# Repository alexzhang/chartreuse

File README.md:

# chartreuse
Project Chartreuse: A touchscreen conbadge powered by Liiiinux!

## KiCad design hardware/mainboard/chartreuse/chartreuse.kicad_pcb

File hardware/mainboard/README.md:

# mainboard
The mainboard of the badge integrates:
- lithium-ion battery charge controller
- TTL LCD display driver
- sound card, amplifier, and speaker
- buttons, charging port, and indicator LEDs

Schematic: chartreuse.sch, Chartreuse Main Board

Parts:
C401, C402: 10uF; CP_Elec_4x5.8
FB1: BLM18RK601SN1D; R_0603
J1: USB_B_Micro; USB_Micro-B_Molex_47346-0001
J2: USB_B_Micro; Conn-5
J3: LiPo; JST_PH_S2B-PH-SM4-TB_02x2.00mm_Angled
J4: USB_A
U3: LM1117-3.3; SOT-223-3_TabPin2

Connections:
+3V3: C402.1, U3.2 (VO); also elsewhere on the board
+5V: C401.1, J2.1, J4.1, U3.3 (VI); also elsewhere on the board
/Power Supply/VCHARGE: J1.1; also elsewhere on the board
/Power Supply/VLIPO: J3.1; also elsewhere on the board
/USB Hub/USB_DOWN2_DN: J4.2; also elsewhere on the board
/USB Hub/USB_DOWN2_DP: J4.3; also elsewhere on the board
/USB Hub/USB_UP_DN: J2.2; also elsewhere on the board
/USB Hub/USB_UP_DP: J2.3; also elsewhere on the board
unnamed: FB1.1, J1.6

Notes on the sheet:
Charger Input
Raspberry Pi
Female USB-A Flash Drive

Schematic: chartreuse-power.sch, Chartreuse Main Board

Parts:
C101: 10uF; CP_Elec_4x5.8
C102: 10uF; C_0805
C103: 0.1uF; C_0402
C104: 2.2uF; C_0805
C105: 100uF; CP_Elec_5x5.8
D101: ORANGE; D_0805
D102: GREEN; D_0805
D103: RED; D_0805
L1: 6.8uH; L_Taiyo-Yuden_NR-40xx_HandSoldering
Q1: MMUN2133LT1G; SOT-23
R101: 270K; R_0402
R102, R104: 100K; R_0402
R103, R111, R112, R113: 1K; R_0402
R105: 15K; R_0402
R106, R109: 1.87M; R_0402
R107: 340K; R_0402
R108, R110: 200K; R_0402
SW1: SW_SPDT; SW_CuK_OS102011MA1QN1_SPDT_Angled
U1: MCP73871; QFN-20-1EP_4x4mm_Pitch0.5mm
U2: TPS61090; QFN-16-1EP_4x4mm_Pitch0.65mm

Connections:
+5V: C104.1, C105.1, R109.1, U2.1, U2.15, U2.16; also elsewhere on the board
/Power Supply/LOW_BATT: Q1.1, U2.12
/Power Supply/PWR_EN: R108.2, SW1.2, U2.11
/Power Supply/VBAT: C102.1, C103.1, L1.1, Q1.2, R106.1, R108.1, U1.1, U1.20, U2.8
/Power Supply/VCHARGE: D101.2, D102.2, R101.1, U1.3, U1.4, U1.9, U1.17, U1.18, U1.19; also elsewhere on the board
/Power Supply/VLIPO: C101.1, U1.14, U1.15, U1.16; also elsewhere on the board
unnamed: D101.1, R112.1
unnamed: D102.1, R113.1
unnamed: D103.2, R111.2
unnamed: L1.2, U2.3, U2.4
unnamed: Q1.3, R111.1
unnamed: R101.2, R102.1, U1.2
unnamed: R103.1, U1.13
unnamed: R104.1, U1.12
unnamed: R105.1, U1.5
unnamed: R106.2, R107.1, U2.9
unnamed: R109.2, R110.1, U2.14
unnamed: R112.2, U1.8
unnamed: R113.2, U1.7

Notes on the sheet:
Ceramic
Ceramic or Tantalum
On/Off Switch

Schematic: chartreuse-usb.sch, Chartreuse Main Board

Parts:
C201, C202, C203: 0.1uF; C_0402
C204: 10uF; C_0805
C205: 1uF; C_0402
C206, C207: 6pF; C_0402
FB2: BLM18RK601SN1D; R_0603
R201, R202, R203, R204: 56K; R_0402
U8: USB2422; QFN-24-1EP_4x4mm_Pitch0.5mm
Y1: 24M; Crystal_SMD_0603-4pin_6.0x3.5mm

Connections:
+3V3: FB2.2; also elsewhere on the board
/Display Controller/TOUCH_DN: U8.2; also elsewhere on the board
/Display Controller/TOUCH_DP: U8.3; also elsewhere on the board
/USB Hub/USB_DOWN2_DN: U8.4; also elsewhere on the board
/USB Hub/USB_DOWN2_DP: U8.5; also elsewhere on the board
/USB Hub/USB_UP_DN: U8.19; also elsewhere on the board
/USB Hub/USB_UP_DP: U8.20; also elsewhere on the board
unnamed: C201.1, C202.1, C203.1, C204.1, FB2.1, R201.1, U8.1, U8.9, U8.15, U8.16, U8.18
unnamed: C205.1, U8.10
unnamed: C206.1, U8.21, Y1.1
unnamed: C207.1, U8.22, Y1.3
unnamed: R201.2, U8.17
unnamed: R202.1, U8.13
unnamed: R203.1, U8.14
unnamed: R204.1, U8.24

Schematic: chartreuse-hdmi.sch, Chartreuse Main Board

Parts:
C301, C302, C303, C304, C326, C327, C328: 10uF; C_0805
C305, C306, C307, C308, C309, C310, C311, C312, C313, C314, C315, C316, C317, C322, C323, C331, C332: 0.1uF; C_0402
C318, C319, C320, C321: 103; C_0402
C324, C325: 12pF; C_0402
C329, C330: 1uF; C_0805
D301: RED; D_0805
D302: BLUE; D_0805
D303: MBR0540; D_SOD-123
D304: MM3Z24VT1G; D_SOD-323
D305: 1N4148; D_SOD-323
FB3, FB4, FB5, FB6, FB7, FB8, FB9: BLM18RK601SN1D; R_0603
FB10, FB11, FB12, FB13: Ferrite_Bead_Small; R_0603
J5: FFC-20; Conn-20
J6: FFC-40; HE10-40D
L2: BRL3225T150K; R_1210
Q2: BSS138; SOT-23
R301, R302, R303, R305, R307: 10K; R_0402
R304, R306: 1K; R_0402
R308: 3; R_0402
R309, R310: 12; R_0402
U4: TFP401A; TQFP-100-1EP_14x14mm_Pitch0.5mm
U5: 24LC02BT-OT; TSOT-23-5
U6: FAN5333; SOT-23-5
U7: AR1100-ISS; SOIC-20W_7.5x12.8mm_Pitch1.27mm
Y2: 12M; Resonator_SMD_muRata_CDSCB-2pin_4.5x2.0mm

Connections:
+3V3: C327.1, D302.2, FB3.2, FB4.2, FB5.2, FB6.2, FB7.1, J6.4; also elsewhere on the board
+5V: C326.1, C328.1, L2.1, R307.1, U6.5; also elsewhere on the board
/Display Controller/24V: C329.1, C330.1, D303.1, D304.1, J6.2
/Display Controller/ACTIVE: D305.1, J6.31, U4.8 (SCDT)
/Display Controller/AGND: C318.2, C319.2, C320.2, C321.2, C322.2, C323.2, C324.2, C325.2, FB8.1, FB9.1, R306.1, U7.6, U7.8, U7.9, U7.13, U7.20
/Display Controller/DISPEN: J6.34, U4.46 (DE)
/Display Controller/HDMI_5V: C332.1, J5.18, J5.19, J5.20, R301.1, R302.2, R303.2, U5.4
/Display Controller/HDMI_DDC_CLK: J5.15, R303.1, U5.1
/Display Controller/HDMI_DDC_DTA: J5.16, R302.1, U5.3
/Display Controller/HDMI_HOTPLUG: J5.17, R301.2
/Display Controller/HDMI_TMDS0_N: J5.8, U4.91 (RX0-)
/Display Controller/HDMI_TMDS0_P: J5.7, U4.90 (RX0+)
/Display Controller/HDMI_TMDS1_N: J5.5, U4.86 (RX1-)
/Display Controller/HDMI_TMDS1_P: J5.4, U4.85 (RX1+)
/Display Controller/HDMI_TMDS2_N: J5.2, U4.81 (RX2-)
/Display Controller/HDMI_TMDS2_P: J5.1, U4.80 (RX2+)
/Display Controller/HDMI_TMDSC_N: J5.11, U4.94 (RXC-)
/Display Controller/HDMI_TMDSC_P: J5.10, U4.93 (RXC+)
/Display Controller/HSYNC: J6.32, U4.48 (HSYNC)
/Display Controller/LEDK: C331.1, D304.2, J6.1, R308.1, R309.1, R310.1, U6.3
/Display Controller/OUT_B0: J6.21, U4.10 (QE0)
/Display Controller/OUT_B1: J6.22, U4.11 (QE1)
/Display Controller/OUT_B2: J6.23, U4.12 (QE2)
/Display Controller/OUT_B3: J6.24, U4.13 (QE3)
/Display Controller/OUT_B4: J6.25, U4.14 (QE4)
/Display Controller/OUT_B5: J6.26, U4.15 (QE5)
/Display Controller/OUT_B6: J6.27, U4.16 (QE6)
/Display Controller/OUT_B7: J6.28, U4.17 (QE7)
/Display Controller/OUT_G0: J6.13, U4.20 (QE8)
/Display Controller/OUT_G1: J6.14, U4.21 (QE9)
/Display Controller/OUT_G2: J6.15, U4.22 (QE10)
/Display Controller/OUT_G3: J6.16, U4.23 (QE11)
/Display Controller/OUT_G4: J6.17, U4.24 (QE12)
/Display Controller/OUT_G5: J6.18, U4.25 (QE13)
/Display Controller/OUT_G6: J6.19, U4.26 (QE14)
/Display Controller/OUT_G7: J6.20, U4.27 (QE15)
/Display Controller/OUT_R0: J6.5, U4.30 (QE16)
/Display Controller/OUT_R1: J6.6, U4.31 (QE17)
/Display Controller/OUT_R2: J6.7, U4.32 (QE18)
/Display Controller/OUT_R3: J6.8, U4.33 (QE19)
/Display Controller/OUT_R4: J6.9, U4.34 (QE20)
/Display Controller/OUT_R5: J6.10, U4.35 (QE21)
/Display Controller/OUT_R6: J6.11, U4.36 (QE22)
/Display Controller/OUT_R7: J6.12, U4.37 (QE23)
/Display Controller/PIXCLK: J6.30, U4.44 (ODCK)
/Display Controller/TOUCH_DN: U7.18; also elsewhere on the board
/Display Controller/TOUCH_DP: U7.19; also elsewhere on the board
/Display Controller/VSYNC: J6.33, U4.47 (VSYNC)
/Display Controller/XN: C320.1, FB12.2, R305.2, U7.14
/Display Controller/XP: C318.1, FB10.2, U7.7
/Display Controller/YN: C321.1, FB13.2, U7.16
/Display Controller/YP: C319.1, FB11.2, U7.15
unnamed: C301.1, C305.1, C306.1, C307.1, FB3.1, U4.4 (PIXS), U4.6 (DVDD), U4.38 (DVDD), U4.67 (DVDD), U4.99 (RSVD), U4.100 (OCK_INV)
unnamed: C302.1, C308.1, C309.1, C310.1, C311.1, C312.1, FB4.1, U4.18 (OVDD), U4.29 (OVDD), U4.43 (OVDD), U4.57 (OVDD), U4.78 (OVDD)
unnamed: C303.1, C313.1, C314.1, C315.1, C316.1, FB5.1, U4.82 (AVDD), U4.84 (AVDD), U4.88 (AVDD), U4.95 (AVDD)
unnamed: C304.1, C317.1, FB6.1, U4.97 (PVDD)
unnamed: C322.1, FB7.2, U7.1, U7.4
unnamed: C323.1, U7.17
unnamed: C324.1, U7.3, Y2.1
unnamed: C325.1, U7.2, Y2.2
unnamed: D301.1, R306.2
unnamed: D301.2, U7.5
unnamed: D302.1, R304.1
unnamed: D303.2, L2.2, U6.1
unnamed: D305.2, R307.2, U6.4
unnamed: FB10.1, J6.37
unnamed: FB11.1, J6.38
unnamed: FB12.1, J6.39
unnamed: FB13.1, J6.40
unnamed: R305.1, U7.11

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
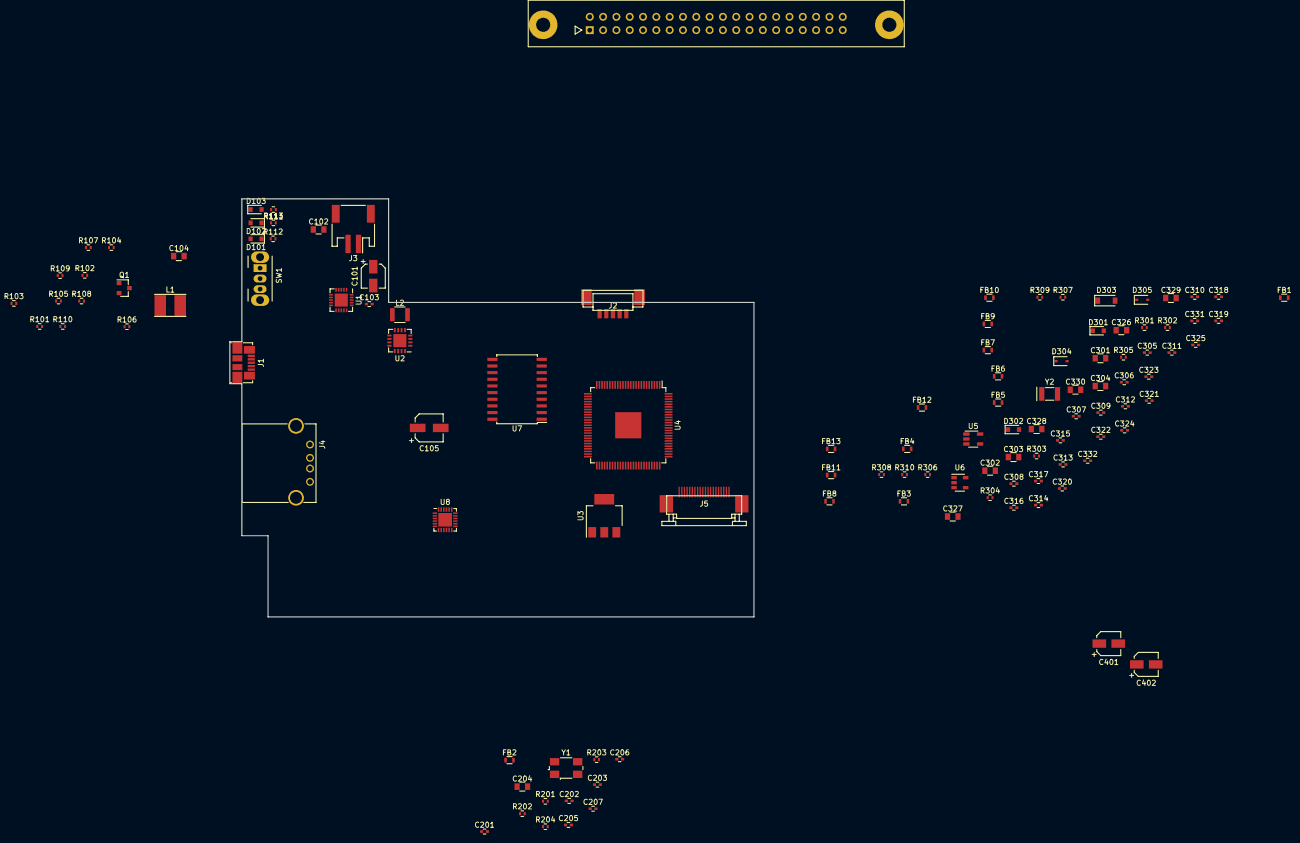
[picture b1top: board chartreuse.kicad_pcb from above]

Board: 4 copper layers, 100.0 x 79.8 mm, 114 parts (0 on the bottom side), 102 nets, no tracks yet.

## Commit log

2018-04-18 Add basic pygame test code
2018-04-19 Set up game loop structure
2018-04-27 Add gitignore for CAD files
2018-04-27 Add mouse position detection
2018-05-07 Initialize KiCAD project
2018-06-09 Add scripts for sound playback over PWM
2018-06-11 Update KiCad project for KiCadv5
2018-06-11 Add power supply schematic sheet
    Added a hierarchical sheet for power circuit and TPS61090 boost converter.
2018-09-19 Add project-specific component library
    Create components for TFP401, AR1100, 24LC02, USB2422, and FAN5333. In addition, add schematic sheets for HDMI and USB subsections.
2018-09-20 Add to HDMI circuit U4, U5, U6, U7, and U8
2018-09-20 Finish HDMI circuit (mostly)
    Added most of the connections and minor components in the HDMI sheet. In addition, added the USB hub IC to the USB sheet.
2018-09-20 Finish USB circuit
2018-09-20 Change USB downstream port 1 to be non-removable
2018-09-21 Add component references
2018-09-21 Schematic DRC check
2018-09-21 Preliminary assign footprints
2018-11-23 Add preliminary PCB outline
2018-11-24 Revise component numbering and footprints
2018-11-24 Add netlist to PCB design
